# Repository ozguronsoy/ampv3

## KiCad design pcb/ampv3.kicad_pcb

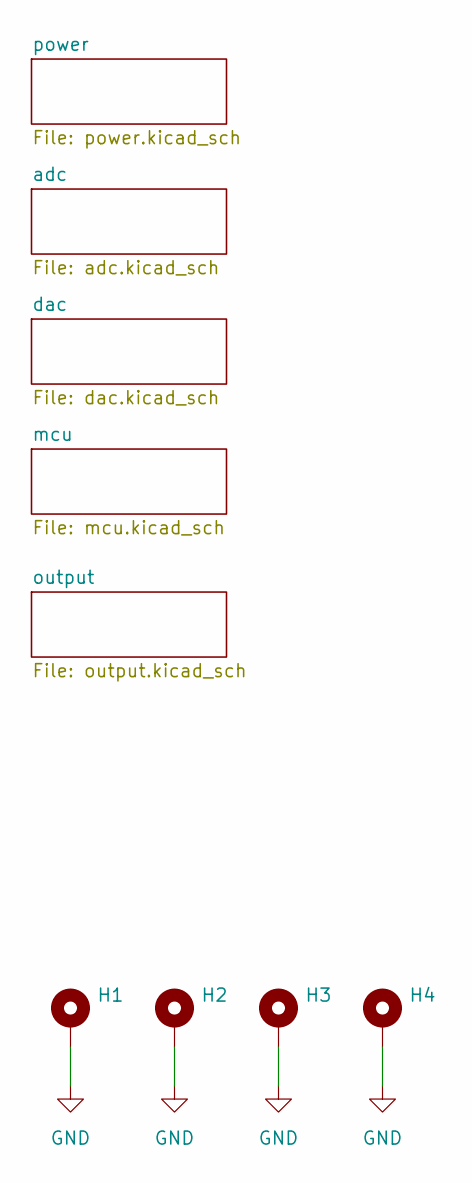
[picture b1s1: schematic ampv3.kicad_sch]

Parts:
H1, H2, H3, H4: MountingHole_Pad; MountingHole_4.3mm_M4_Pad

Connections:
GND: H1.1 (1_1), H2.1 (1_1), H3.1 (1_1), H4.1 (1_1); also elsewhere on the board

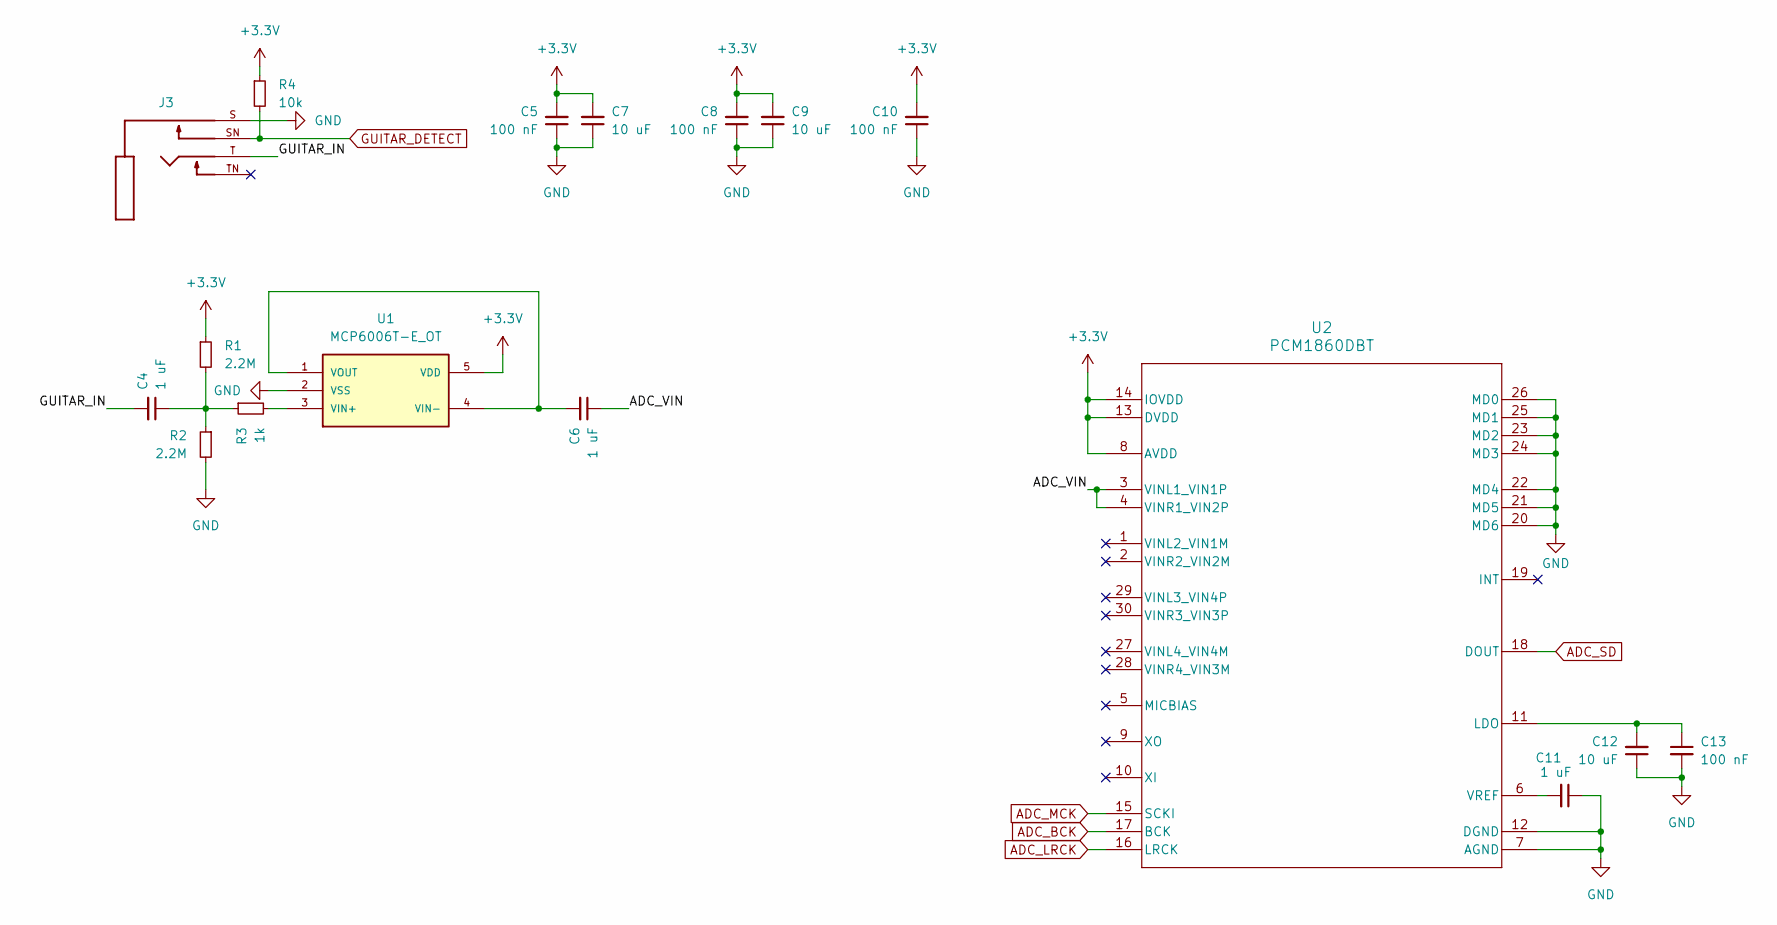
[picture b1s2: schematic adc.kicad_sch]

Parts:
C4, C6, C11: 1 uF; C_0603_1608Metric
C5, C8, C10, C13: 100 nF; C_0603_1608Metric
C7, C9, C12: 10 uF; C_0603_1608Metric
J3: ACJMIH; PARTREV 2
R1, R2: 2.2M; R_0603_1608Metric
R3: 1k; R_0603_1608Metric
R4: 10k; R_0603_1608Metric
U1: MCP6006T-E_OT; SC-74A-5_1.55x2.9mm_P0.95mm; MPN MCP6006UT-E/LT
U2: PCM1860DBT

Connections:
+3.3V: C5.2, C7.2, C8.2, C9.2, C10.2, R1.1, R4.1, U1.5 (VDD), U2.8 (AVDD), U2.13 (DVDD), U2.14 (IOVDD); also elsewhere on the board
/adc/ADC_VIN: C6.1, U2.3 (VINL1_VIN1P), U2.4 (VINR1_VIN2P)
/adc/GUITAR_IN: C4.2, J3.T
ADC_BCK: U2.17 (BCK); also elsewhere on the board
ADC_LRCK: U2.16 (LRCK); also elsewhere on the board
ADC_MCK: U2.15 (SCKI); also elsewhere on the board
ADC_SD: U2.18 (DOUT); also elsewhere on the board
GND: C5.1, C7.1, C8.1, C9.1, C10.1, C11.1, C12.1, C13.2, J3.S, R2.2, U1.2 (VSS), U2.7 (AGND), U2.12 (DGND), U2.20 (MD6), U2.21 (MD5), U2.22 (MD4), U2.23 (MD2), U2.24 (MD3), U2.25 (MD1), U2.26 (MD0); also elsewhere on the board
GUITAR_DETECT: J3.SN, R4.2; also elsewhere on the board
unnamed: C4.1, R1.2, R2.1, R3.1
unnamed: R3.2, U1.3 (VIN+)
unnamed: C6.2, U1.1 (VOUT), U1.4 (VIN-)
unnamed: C12.2, C13.1, U2.11 (LDO)
unnamed: C11.2, U2.6 (VREF)

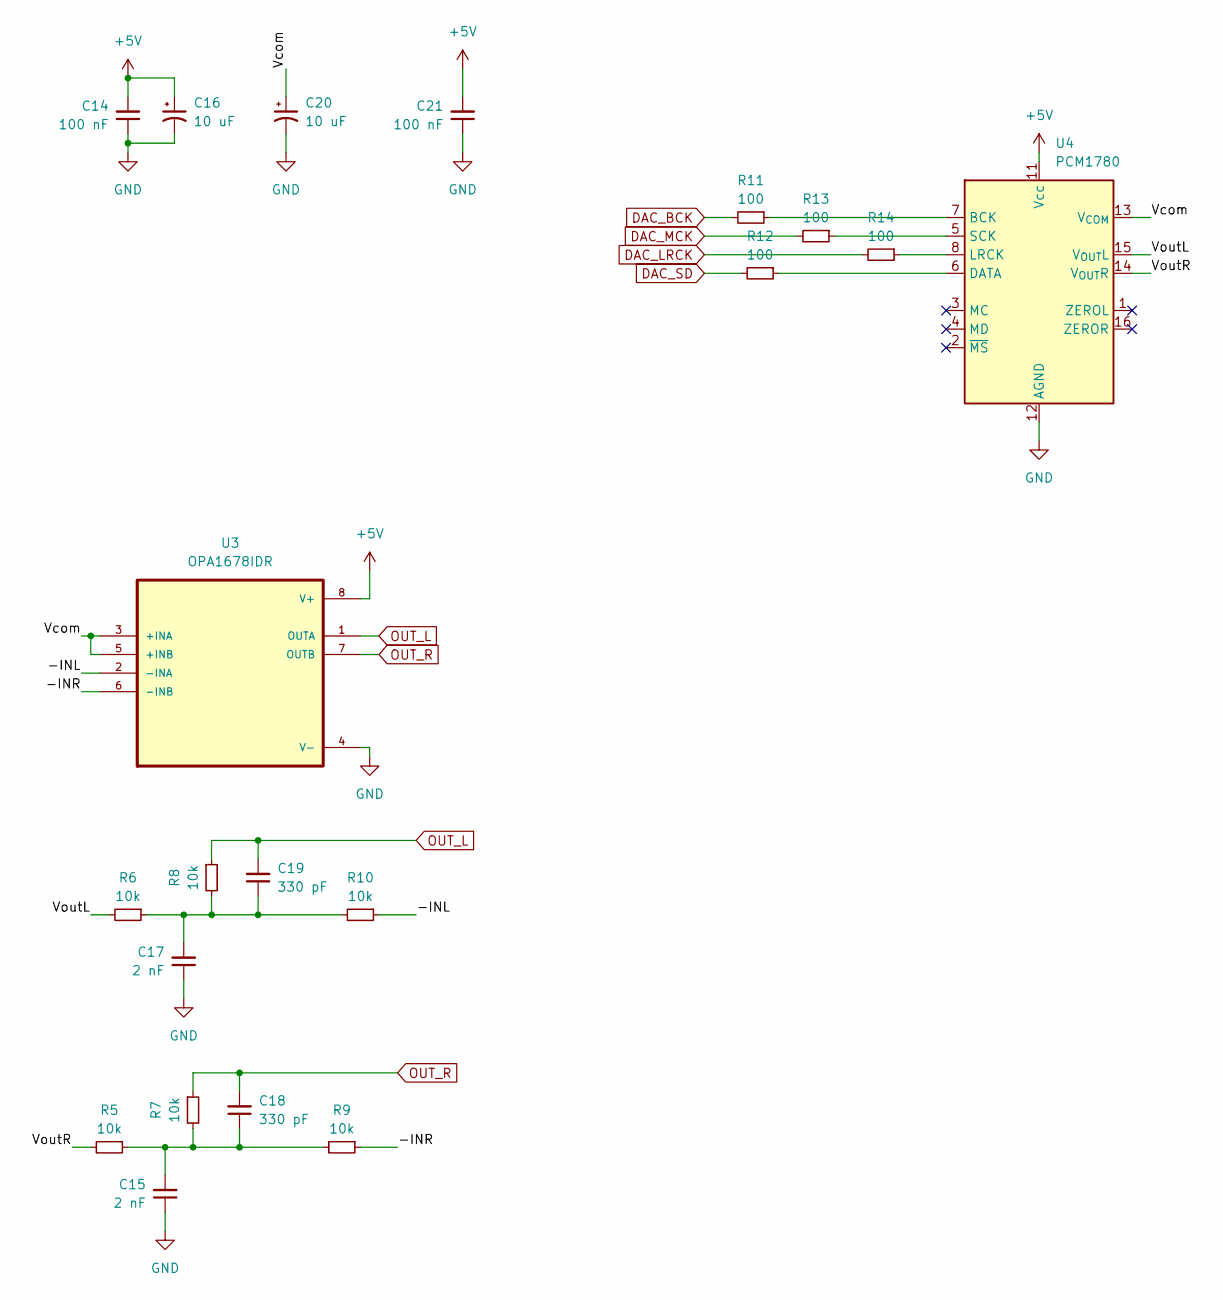
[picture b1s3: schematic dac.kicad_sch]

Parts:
C14, C21: 100 nF; C_0603_1608Metric
C15, C17: 2 nF; C_0603_1608Metric
C16, C20: 10 uF; CP_Elec_5x5.3
C18, C19: 330 pF; C_0603_1608Metric
R5, R6, R7, R8, R9, R10: 10k; R_0603_1608Metric
R11, R12, R13, R14: 100; R_0603_1608Metric
U3: OPA1678IDR
U4: PCM1780; SSOP-16_3.9x4.9mm_P0.635mm

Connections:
+5V: C14.2, C16.1, C21.2, U3.8 (V+), U4.11 (Vcc); also elsewhere on the board
/dac/-INL: R10.1, U3.2 (-INA)
/dac/-INR: R9.1, U3.6 (-INB)
/dac/Vcom: C20.1, U3.3 (+INA), U3.5 (+INB), U4.13 (V_{COM})
/dac/VoutL: R6.2, U4.15 (V_{OUT}L)
/dac/VoutR: R5.2, U4.14 (V_{OUT}R)
DAC_BCK: R11.2; also elsewhere on the board
DAC_LRCK: R14.2; also elsewhere on the board
DAC_MCK: R13.2; also elsewhere on the board
DAC_SD: R12.2; also elsewhere on the board
GND: C14.1, C15.1, C16.2, C17.1, C20.2, C21.1, U3.4 (V-), U4.12 (AGND); also elsewhere on the board
unnamed: C15.2, C18.1, R5.1, R7.2, R9.2
unnamed: C17.2, C19.1, R6.1, R8.2, R10.2
unnamed: R11.1, U4.7 (BCK)
unnamed: R12.1, U4.6 (DATA)
unnamed: R14.1, U4.8 (LRCK)
unnamed: R13.1, U4.5 (SCK)
OUT_L: C19.2, R8.1, U3.1 (OUTA); also elsewhere on the board
OUT_R: C18.2, R7.1, U3.7 (OUTB); also elsewhere on the board

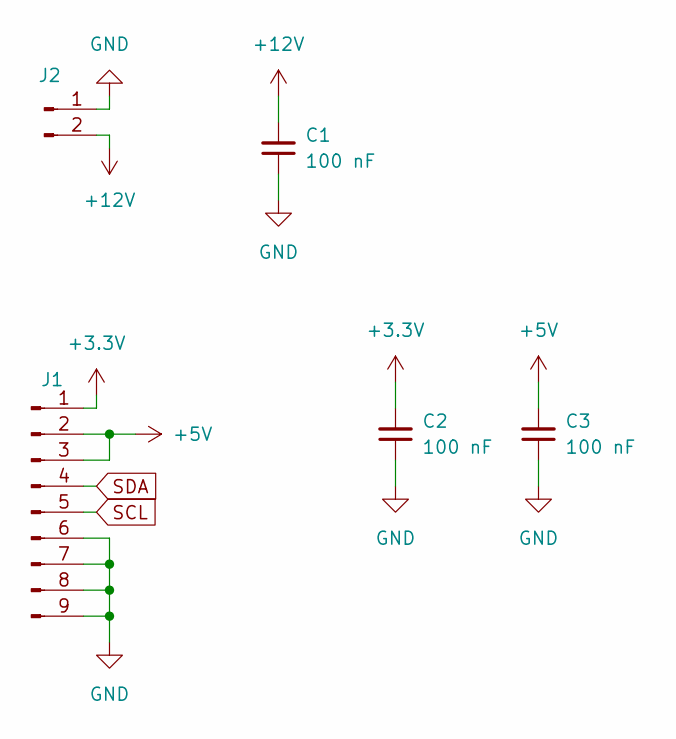
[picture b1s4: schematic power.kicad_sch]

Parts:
C1, C2, C3: 100 nF; C_0603_1608Metric
J1: JST_EH_B9B-EH-A_1x09_P2.50mm_Vertical
J2: Conn_01x02_Pin; AMASS_XT30PW-M_1x02_P2.50mm_Horizontal

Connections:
+3.3V: C2.2, J1.1; also elsewhere on the board
+5V: C3.2, J1.2, J1.3; also elsewhere on the board
+12V: C1.2, J2.2; also elsewhere on the board
GND: C1.1, C2.1, C3.1, J1.6, J1.7, J1.8, J1.9, J2.1; also elsewhere on the board
SCL: J1.5; also elsewhere on the board
SDA: J1.4; also elsewhere on the board

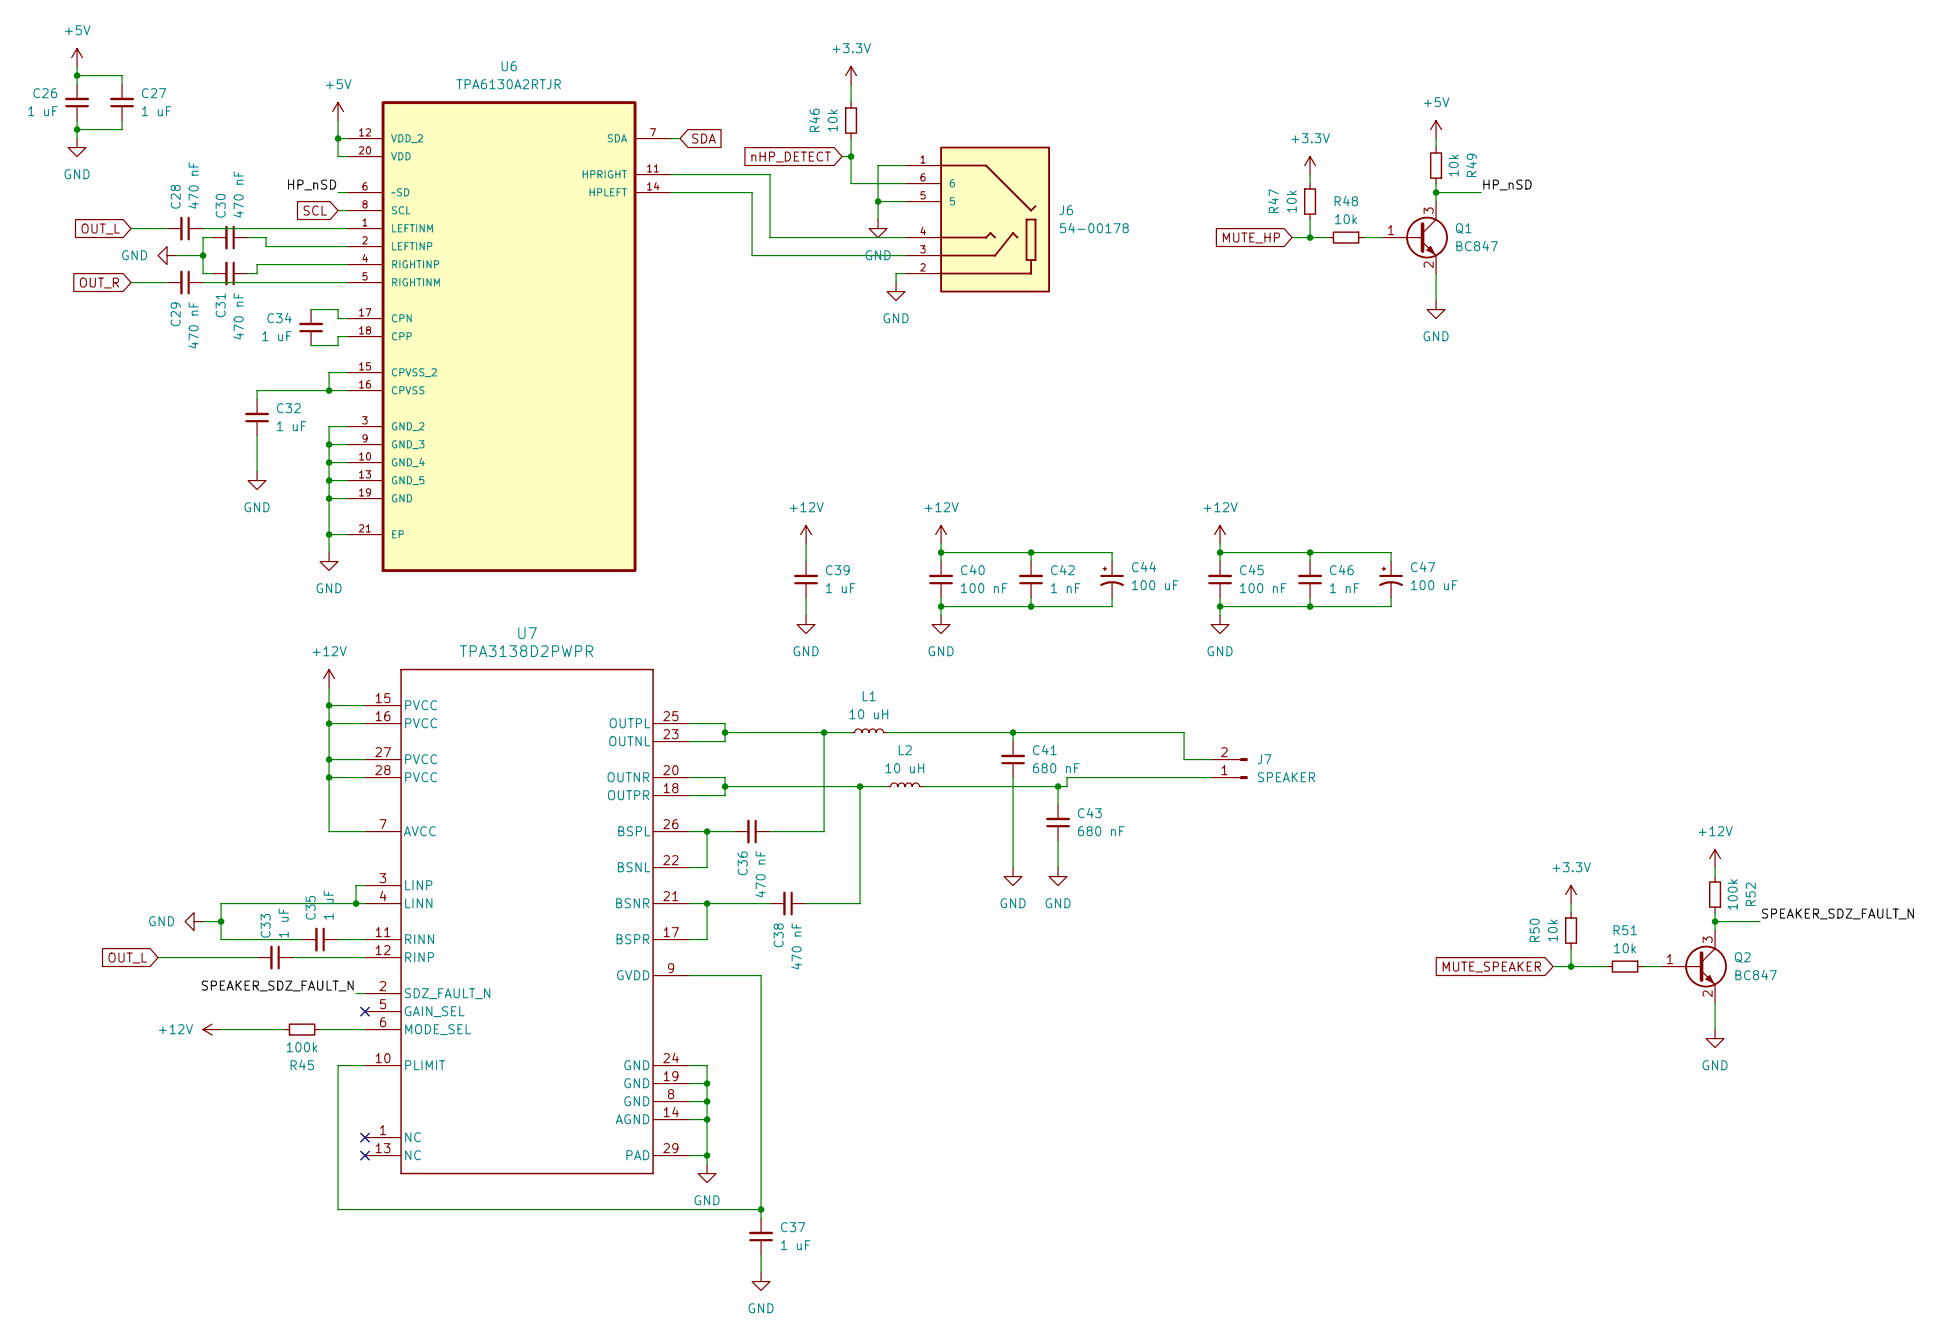
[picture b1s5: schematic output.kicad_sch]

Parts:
C26, C27, C32, C33, C34, C35, C37, C39: 1 uF; C_0603_1608Metric
C28, C29, C30, C31, C36, C38: 470 nF; C_0603_1608Metric
C40, C45: 100 nF; C_0603_1608Metric
C41, C43: 680 nF; C_0603_1608Metric
C42, C46: 1 nF; C_0603_1608Metric
C44, C47: 100 uF; CP_Elec_5x5.3
J6: 54-00178; PARTREV A
J7: SPEAKER; PinHeader_1x02_P2.54mm_Vertical
L1, L2: 10 uH; L_Changjiang_FNR6028S
Q1, Q2: BC847; SOT-23
R45, R52: 100k; R_0603_1608Metric
R46, R47, R48, R49, R50, R51: 10k; R_0603_1608Metric
U6: TPA6130A2RTJR; MPN TPA6130A2RTJR
U7: TPA3138D2PWPR

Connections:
+3.3V: R46.1, R47.1, R50.1; also elsewhere on the board
+5V: C26.2, C27.2, R49.2, U6.12 (VDD_2), U6.20 (VDD); also elsewhere on the board
+12V: C39.2, C40.2, C42.2, C44.1, C45.2, C46.2, C47.1, R45.1, R52.2, U7.7 (AVCC), U7.15 (PVCC), U7.16 (PVCC), U7.27 (PVCC), U7.28 (PVCC); also elsewhere on the board
/output/HP_nSD: Q1.3 (C), R49.1, U6.6 (~SD)
/output/SPEAKER_SDZ_FAULT_N: Q2.3 (C), R52.1, U7.2 (SDZ_FAULT_N)
GND: C26.1, C27.1, C30.2, C31.2, C32.1, C35.2, C37.1, C39.1, C40.1, C41.1, C42.1, C43.1, C44.2, C45.1, C46.1, C47.2, J6.1, J6.2, J6.5, Q1.2 (E), Q2.2 (E), U6.3 (GND_2), U6.9 (GND_3), U6.10 (GND_4), U6.13 (GND_5), U6.19 (GND), U6.21 (EP), U7.3 (LINP), U7.4 (LINN), U7.8 (GND), U7.14 (AGND), U7.19 (GND), U7.24 (GND), U7.29 (PAD); also elsewhere on the board
MUTE_HP: R47.2, R48.2; also elsewhere on the board
MUTE_SPEAKER: R50.2, R51.2; also elsewhere on the board
unnamed: C43.2, J7.1, L2.2
unnamed: C41.2, J7.2, L1.2
unnamed: Q1.1 (B), R48.1
unnamed: Q2.1 (B), R51.1
unnamed: C34.2, U6.17 (CPN)
unnamed: C34.1, U6.18 (CPP)
unnamed: C32.2, U6.15 (CPVSS_2), U6.16 (CPVSS)
unnamed: J6.3, U6.14 (HPLEFT)
unnamed: J6.4, U6.11 (HPRIGHT)
unnamed: C28.1, U6.1 (LEFTINM)
unnamed: C30.1, U6.2 (LEFTINP)
unnamed: C29.1, U6.5 (RIGHTINM)
unnamed: C31.1, U6.4 (RIGHTINP)
unnamed: C36.2, U7.22 (BSNL), U7.26 (BSPL)
unnamed: C38.2, U7.17 (BSPR), U7.21 (BSNR)
unnamed: C37.2, U7.9 (GVDD), U7.10 (PLIMIT)
unnamed: R45.2, U7.6 (MODE_SEL)
unnamed: C36.1, L1.1, U7.23 (OUTNL), U7.25 (OUTPL)
unnamed: C38.1, L2.1, U7.18 (OUTPR), U7.20 (OUTNR)
unnamed: C35.1, U7.11 (RINN)
unnamed: C33.1, U7.12 (RINP)
OUT_L: C28.2, C33.2; also elsewhere on the board
OUT_R: C29.2; also elsewhere on the board
SCL: U6.8 (SCL); also elsewhere on the board
SDA: U6.7 (SDA); also elsewhere on the board
nHP_DETECT: J6.6, R46.2; also elsewhere on the board

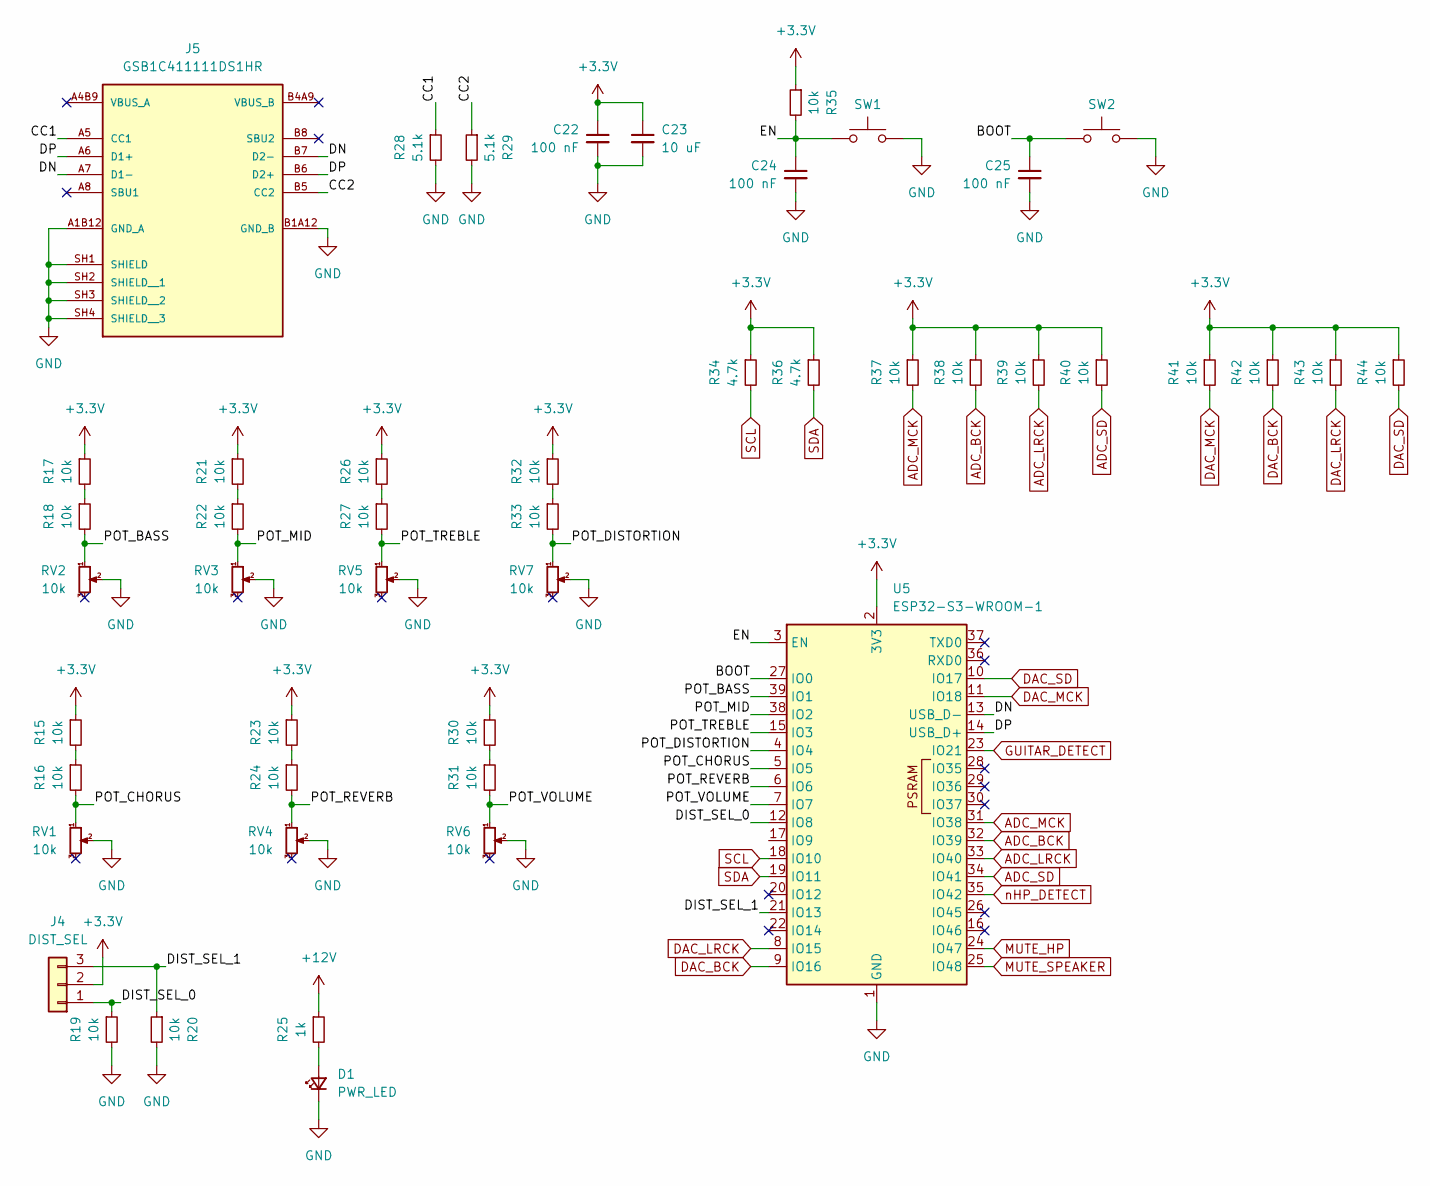
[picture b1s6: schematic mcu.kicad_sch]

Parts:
C22, C24, C25: 100 nF; C_0603_1608Metric
C23: 10 uF; C_0603_1608Metric
D1: PWR_LED; LED_D5.0mm
J4: DIST_SEL; PinHeader_1x03_P2.54mm_Vertical
J5: GSB1C411111DS1HR; PARTREV AX3
R15, R16, R17, R18, R19, R20, R21, R22, R23, R24, R26, R27, R30, R31, R32, R33, R35, R37, R38, R39, R40, R41, R42, R43, R44: 10k; R_0603_1608Metric
R25: 1k; R_0603_1608Metric
R28, R29: 5.1k; R_0603_1608Metric
R34, R36: 4.7k; R_0603_1608Metric
RV1, RV2, RV3, RV4, RV5, RV6, RV7: 10k; POT_CUSTOM
SW1, SW2: SW_Push; SW_Tactile_SPST_NO_Straight_CK_PTS636Sx25SMTRLFS
U5: ESP32-S3-WROOM-1

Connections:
+3.3V: C22.1, C23.1, J4.2, R15.1, R17.1, R21.1, R23.1, R26.1, R30.1, R32.1, R34.1, R35.1, R36.1, R37.1, R38.1, R39.1, R40.1, R41.1, R42.1, R43.1, R44.1, U5.2 (3V3); also elsewhere on the board
+12V: R25.1; also elsewhere on the board
/mcu/BOOT: C25.1, SW2.1, U5.27 (IO0)
/mcu/CC1: J5.A5 (CC1), R28.1
/mcu/CC2: J5.B5 (CC2), R29.1
/mcu/DIST_SEL_0: J4.1, R19.1, U5.12 (IO8)
/mcu/DIST_SEL_1: J4.3, R20.1, U5.21 (IO13)
/mcu/DN: J5.A7 (D1-), J5.B7 (D2-), U5.13 (USB_D-)
/mcu/DP: J5.A6 (D1+), J5.B6 (D2+), U5.14 (USB_D+)
/mcu/EN: C24.1, R35.2, SW1.1, U5.3 (EN)
/mcu/POT_BASS: R18.2, RV2.1, U5.39 (IO1)
/mcu/POT_CHORUS: R16.2, RV1.1, U5.5 (IO5)
/mcu/POT_DISTORTION: R33.2, RV7.1, U5.4 (IO4)
/mcu/POT_MID: R22.2, RV3.1, U5.38 (IO2)
/mcu/POT_REVERB: R24.2, RV4.1, U5.6 (IO6)
/mcu/POT_TREBLE: R27.2, RV5.1, U5.15 (IO3)
/mcu/POT_VOLUME: R31.2, RV6.1, U5.7 (IO7)
ADC_BCK: R38.2, U5.32 (IO39); also elsewhere on the board
ADC_LRCK: R39.2, U5.33 (IO40); also elsewhere on the board
ADC_MCK: R37.2, U5.31 (IO38); also elsewhere on the board
ADC_SD: R40.2, U5.34 (IO41); also elsewhere on the board
DAC_BCK: R42.2, U5.9 (IO16); also elsewhere on the board
DAC_LRCK: R43.2, U5.8 (IO15); also elsewhere on the board
DAC_MCK: R41.2, U5.11 (IO18); also elsewhere on the board
DAC_SD: R44.2, U5.10 (IO17); also elsewhere on the board
GND: C22.2, C23.2, C24.2, C25.2, D1.1 (K), J5.A1B12 (GND_A), J5.B1A12 (GND_B), J5.SH1 (SHIELD), J5.SH2 (SHIELD__1), J5.SH3 (SHIELD__2), J5.SH4 (SHIELD__3), R19.2, R20.2, R28.2, R29.2, RV1.2, RV2.2, RV3.2, RV4.2, RV5.2, RV6.2, RV7.2, SW1.2, SW2.2, U5.1 (GND), U5.40 (GND), U5.41 (GND); also elsewhere on the board
GUITAR_DETECT: U5.23 (IO21); also elsewhere on the board
MUTE_HP: U5.24 (IO47); also elsewhere on the board
MUTE_SPEAKER: U5.25 (IO48); also elsewhere on the board
unnamed: D1.2 (A), R25.2
unnamed: R15.2, R16.1
unnamed: R17.2, R18.1
unnamed: R21.2, R22.1
unnamed: R23.2, R24.1
unnamed: R26.2, R27.1
unnamed: R30.2, R31.1
unnamed: R32.2, R33.1
SCL: R34.2, U5.18 (IO10); also elsewhere on the board
SDA: R36.2, U5.19 (IO11); also elsewhere on the board
nHP_DETECT: U5.35 (IO42); also elsewhere on the board

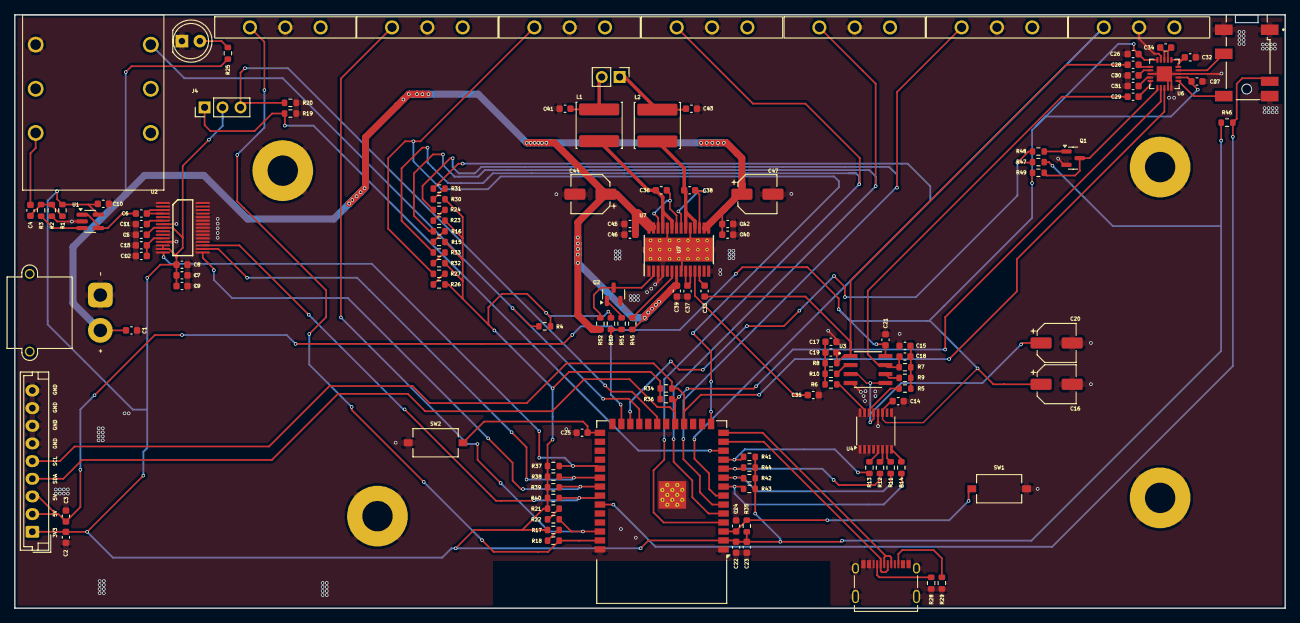
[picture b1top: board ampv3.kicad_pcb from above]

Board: 2 copper layers, 179.8 x 84.0 mm, 131 parts (0 on the bottom side), 84 nets.

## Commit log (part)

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2025-11-21 add buffer to guitar input, add effect pots
2025-11-23 finished schematics
2025-11-25 finished most of the routing
2025-11-25 finished routing
